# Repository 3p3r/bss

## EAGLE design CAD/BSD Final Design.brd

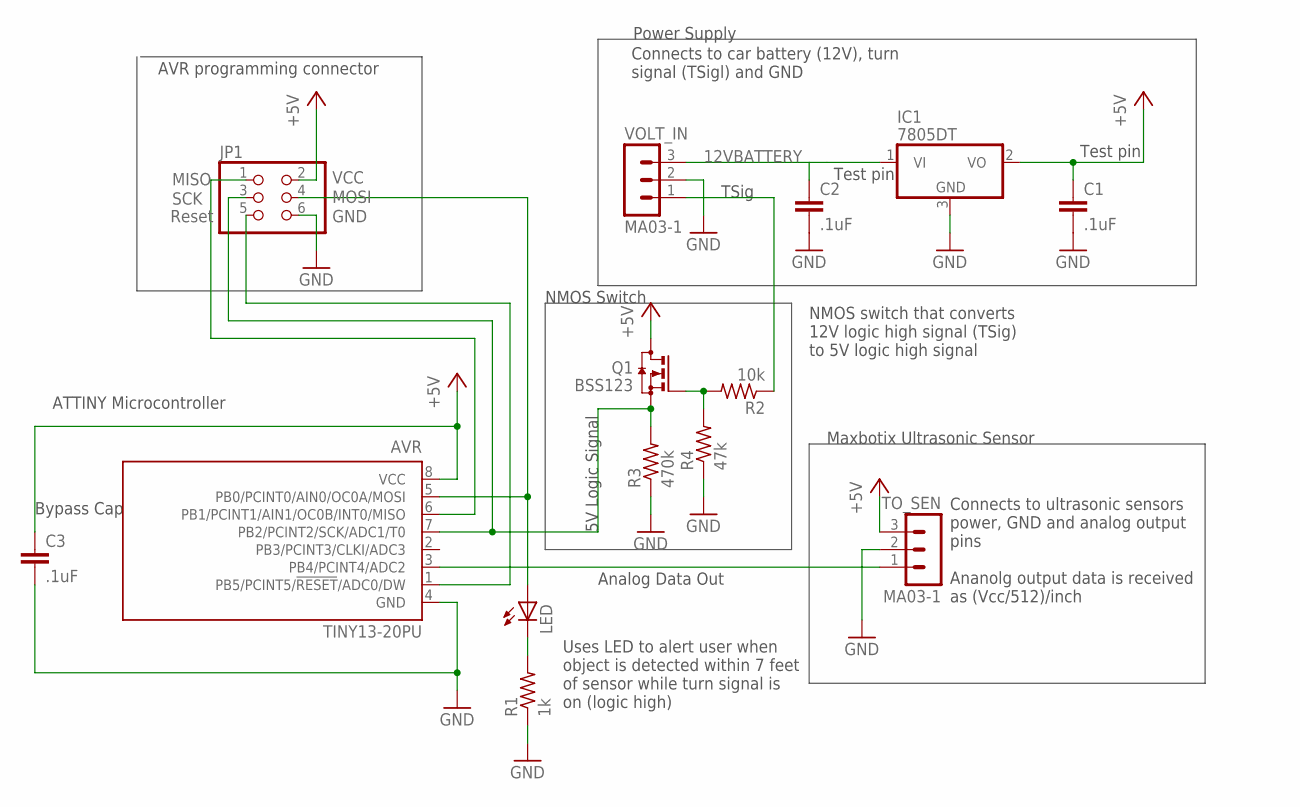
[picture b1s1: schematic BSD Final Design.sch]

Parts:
AVR: TINY13-20PU; DIL08
C1, C2, C3: .1uF; C0805
IC1: 7805DT; TO252
JP1: PINHD-2X3; 2X03
LED: LED5MM
Q1: BSS123; SOT23
R1: 1k; R0805
R2: 10k; R0805
R3: 470k; R0805
R4: 47k; R0805
TO_SEN: MA03-1
VOLT_IN: MA03-1

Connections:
2N7000: AVR.7 (PB2/PCINT2/SCK/ADC1/T0), JP1.3, Q1.2 (S), R3.2
12VBATTERY: C2.1, IC1.1 (VI), VOLT_IN.3
+5V: AVR.8 (VCC), C1.1, C3.1, IC1.2 (VO), JP1.2, Q1.3 (D), TO_SEN.3
GND: AVR.4 (GND), C1.2, C2.2, C3.2, IC1.3 (GND), JP1.6, R1.1, R3.1, R4.1, TO_SEN.2, VOLT_IN.2
unnamed: AVR.3 (PB4/PCINT4/ADC2), TO_SEN.1
unnamed: AVR.5 (PB0/PCINT0/AIN0/OC0A/MOSI), JP1.4, LED.A
unnamed: R2.1, VOLT_IN.1
unnamed: Q1.1 (G), R2.2, R4.2
unnamed: AVR.1 (PB5/PCINT5/!RESET!/ADC0/DW), JP1.5
unnamed: AVR.6 (PB1/PCINT1/AIN1/OC0B/INT0/MISO), JP1.1
RLED: LED.K (C), R1.2

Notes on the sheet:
Bypass Cap
Power Supply
Connects to ultrasonic sensors power, GND and analog output pins Ananolg output data is received as (Vcc/512)/inch
Connects to car battery (12V), turn signal (TSigl) and GND
ATTINY Microcontroller
Test pin
MISO
SCK
Reset
VCC
MOSI
GND
AVR programming connector
Uses LED to alert user when object is detected within 7 feet of sensor while turn signal is on (logic high)
NMOS switch that converts 12V logic high signal (TSig) to 5V logic high signal
NMOS Switch
Maxbotix Ultrasonic Sensor
Analog Data Out
TSig
5V Logic Signal

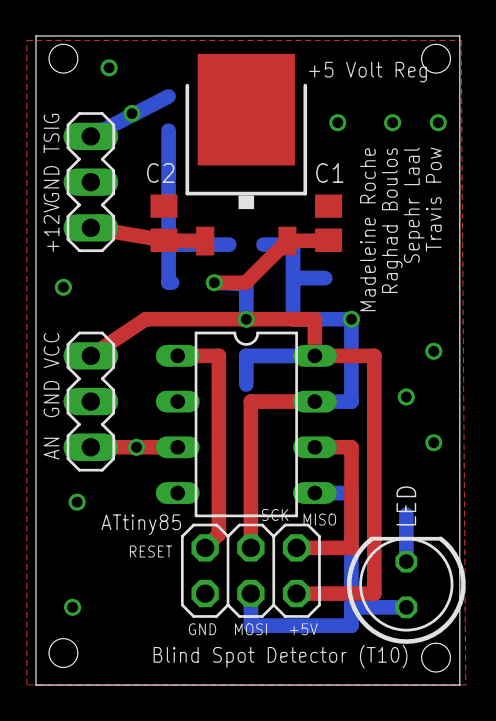
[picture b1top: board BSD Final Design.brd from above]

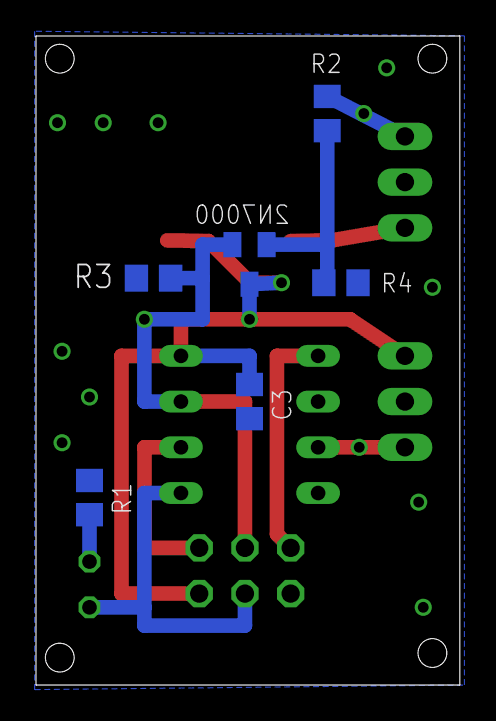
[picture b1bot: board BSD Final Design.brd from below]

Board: 2 copper layers, 23.5 x 36.1 mm, 14 parts (6 on the bottom side), 11 nets.

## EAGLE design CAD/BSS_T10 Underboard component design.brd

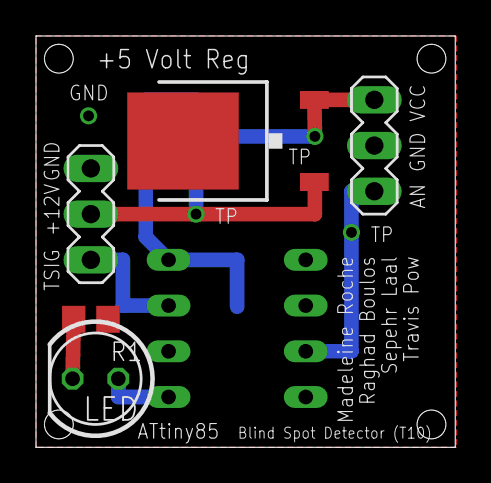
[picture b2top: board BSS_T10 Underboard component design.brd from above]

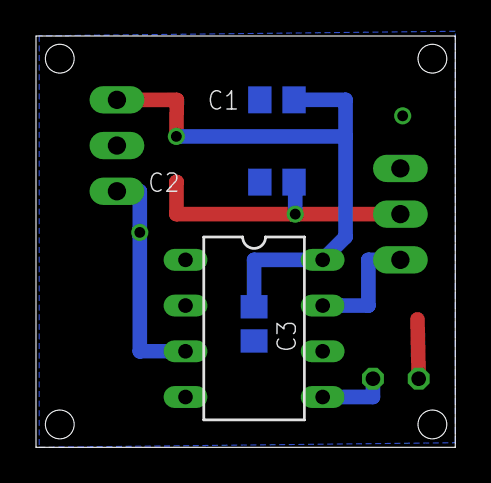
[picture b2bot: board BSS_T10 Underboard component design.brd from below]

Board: 2 copper layers, 23.3 x 22.8 mm, 9 parts (4 on the bottom side), 7 nets.

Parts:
AVR: TINY13-20PU; DIL08
C1, C2, C3: .1uF; C0805
IC1: 7805DT; TO252
LED: LED5MM
R1: 1k; R0805
TO_SEN: MA03-1
VOLT_IN: MA03-1

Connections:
12VBATTERY: C2.1, IC1.1, VOLT_IN.2
+5V: AVR.8, C1.1, C3.1, IC1.2, TO_SEN.3
GND: AVR.4, C1.2, C2.2, C3.2, IC1.3, R1.1, TO_SEN.2, VOLT_IN.1
unnamed: AVR.3, TO_SEN.1
unnamed: AVR.5, LED.A
RLED: LED.K, R1.2
TSIG: AVR.7, VOLT_IN.3

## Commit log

2015-10-11 checked in the very important gif of the wiki homepage
2015-10-24 Cad file update
2015-10-24 Updated wires
2015-10-24 added gitignore to CAD folder
2015-10-26 Readjusted Grid
2015-10-28 Voltage reg and supply
    Power source, turn signal switch, linear voltage regulator and bypass
    caps added to schematic
2015-10-30 Updated connections
    Changed sensor connections to pin headers to main board
2015-11-02 Removed sensor
    Removed sensor from schematic since it is a board of its own and will
    not be on the PCB. Also added a frame.
2015-11-02 Team number
    Added team name to schematic name
2015-11-04 Board Layout
    Uploaded board layout with components on both sides of board
2015-11-05 Project Schedule
2015-11-05 Board labels
    Improved labeling of board
2015-11-09 Different Pins
    Changed pins to AVR
2015-11-09 GND Via
2015-11-09 board
2015-11-13 New Board Layout
2015-11-18 System Block Diagrams
    Level 0 diagrams for system and subsystems, Level 1 diagram for system,
    State Machine for system, Interaction View for system
2015-11-18 Revert "System Block Diagrams"
    This reverts commit ed915570ca9041c14a97283533249c12f19626e5.
2015-11-18 System Design and Modeling
    Level 0 and Level 1 block diagrams for entire system. Level 0 block
    diagrams for subsystems. UML state machine and interaction view for
    system.
2015-11-25 checked in test docs
2015-12-09 Final Design
    Included more documentation
2015-12-09 Revised Test Plan
    Added missing references and tests
2015-12-09 CAD to master
2015-12-10 checked in source code
2015-12-10 Project Schedule Revision #2.0
2015-12-10 Revised System Modeling, Created Project Schedule folder
2015-12-10 Revised Level0 with module table
2015-12-11 updated test cases
2015-12-11 checked in presentation
2015-12-11 BOM commit
